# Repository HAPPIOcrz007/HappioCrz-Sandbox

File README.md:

# HappioCrz-Sandbox
a holderfor trials and learning zone for Happio-Projects and Happio-Wiki

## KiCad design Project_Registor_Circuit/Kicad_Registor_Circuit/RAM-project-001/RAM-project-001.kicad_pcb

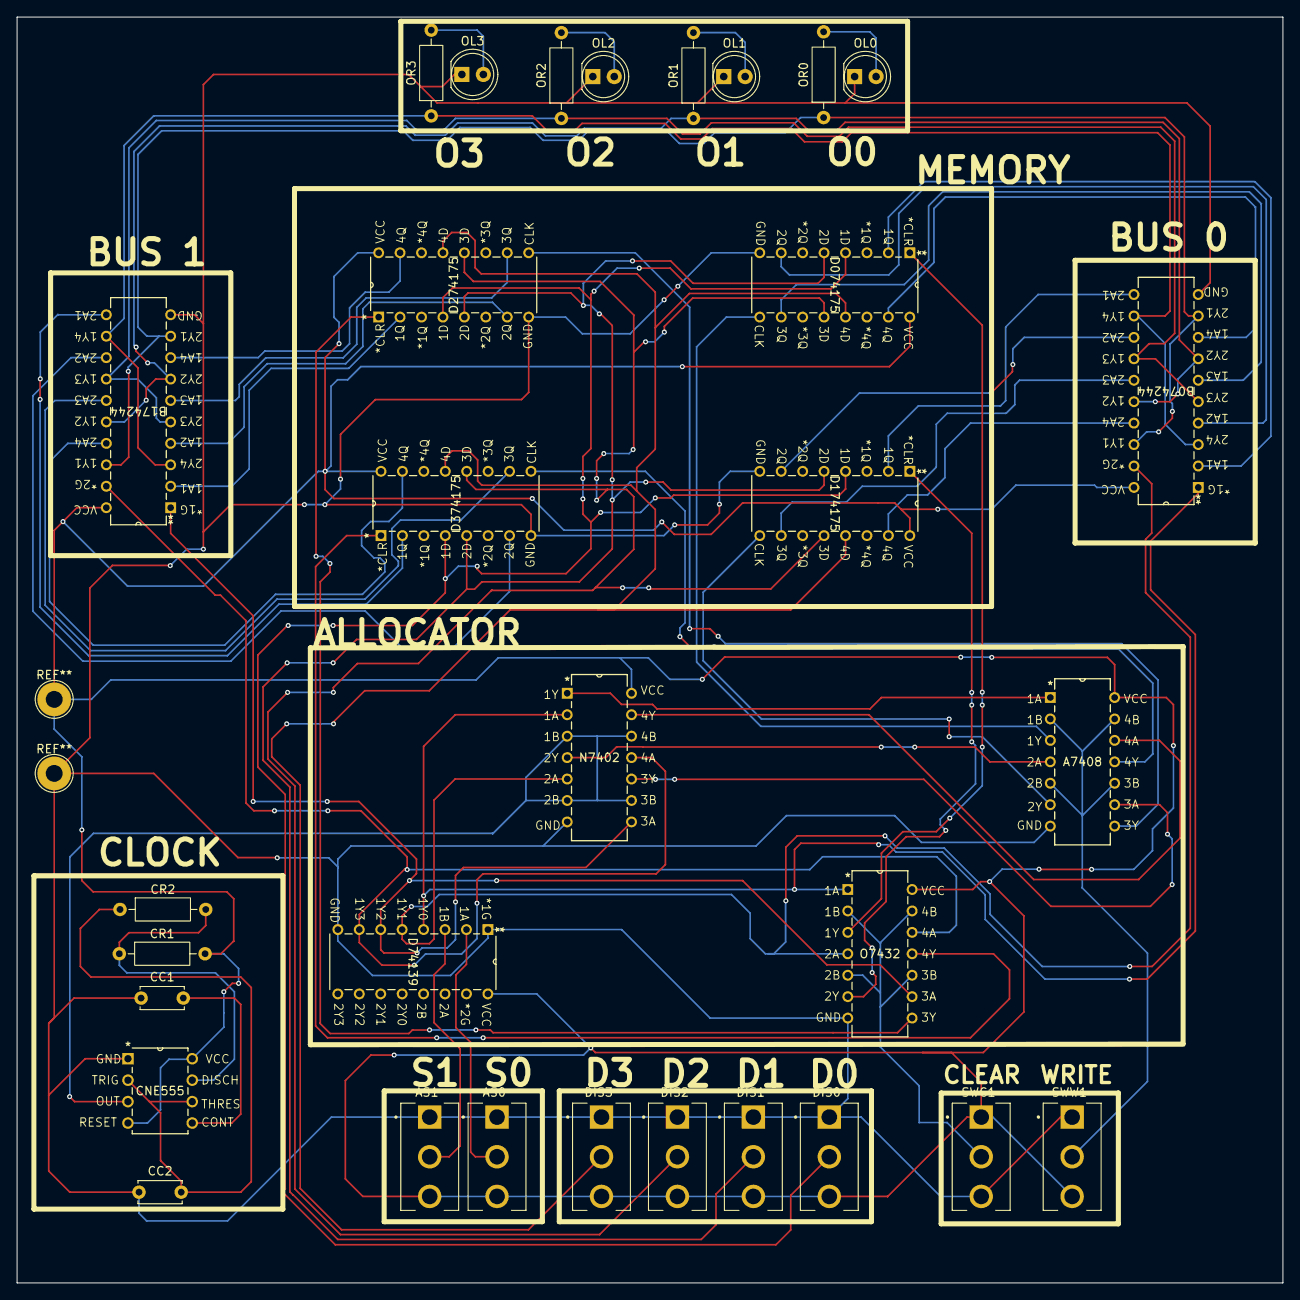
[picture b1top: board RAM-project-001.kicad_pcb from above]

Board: 2 copper layers, 150.0 x 150.0 mm, 31 parts (0 on the bottom side), 54 nets.

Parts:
A7408: A7408; SN74LS08N
AS0: AS0; SW_100SP1T1B4M2QE
AS1: AS1; SW_100SP1T1B4M2QE
B074244: B074244; SN74LS244N
B174244: B174244; SN74LS244N
CC1: CC1; C_Disc_D5.0mm_W2.5mm_P5.00mm
CC2: CC2; C_Disc_D5.0mm_W2.5mm_P5.00mm
CNE555: CNE555; NE555P
CR1: CR1; R_Axial_DIN0207_L6.3mm_D2.5mm_P10.16mm_Horizontal
CR2: CR2; R_Axial_DIN0207_L6.3mm_D2.5mm_P10.16mm_Horizontal
D74139: D74139; SN74LS139AN
D074175: D074175; SN74LS175N
D174175: D174175; SN74LS175N
D274175: D274175; SN74LS175N
D374175: D374175; SN74LS175N
DIS0: DIS0; SW_100SP1T1B4M2QE
DIS1: DIS1; SW_100SP1T1B4M2QE
DIS2: DIS2; SW_100SP1T1B4M2QE
DIS3: DIS3; SW_100SP1T1B4M2QE
N7402: N7402; SN7402N
O7432: O7432; SN7432N
OL0, OL1, OL2, OL3: CQY99; LED_D5.0mm
OR0, OR1, OR2, OR3: R; R_Axial_DIN0207_L6.3mm_D2.5mm_P10.16mm_Horizontal
SWC1: SWC; SW_100SP1T1B4M2QE
SWW1: SWW; SW_100SP1T1B4M2QE

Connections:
+5V: A7408.14 (VCC), AS0.3, AS1.3, B074244.20 (VCC), B174244.20 (VCC), CNE555.4 (RESET), CNE555.8 (VCC), CR1.2, D74139.16 (VCC), D074175.16 (VCC), D174175.16 (VCC), D274175.16 (VCC), D374175.16 (VCC), DIS0.3, DIS1.3, DIS2.3, DIS3.3, N7402.14 (VCC), O7432.14 (VCC), SWC1.1, SWW1.3
/C0: D074175.1 (*CLR), O7432.3 (1Y)
/C1: D174175.1 (*CLR), O7432.6 (2Y)
/C2: D274175.1 (*CLR), O7432.8 (3Y)
/C3: D374175.1 (*CLR), O7432.11 (4Y)
/D0: D074175.4 (1D), D174175.4 (1D), D274175.4 (1D), D374175.4 (1D), DIS0.2
/D1: D074175.5 (2D), D174175.5 (2D), D274175.5 (2D), D374175.5 (2D), DIS1.2
/D2: D074175.12 (3D), D174175.12 (3D), D274175.12 (3D), D374175.12 (3D), DIS2.2
/D3: D074175.13 (4D), D174175.13 (4D), D274175.13 (4D), D374175.13 (4D), DIS3.2
/S0: B074244.1 (*1G), D74139.4 (1Y0), N7402.2 (1A), O7432.1 (1A)
/S1: B074244.19 (*G/2G), D74139.5 (1Y1), N7402.5 (2A), O7432.4 (2A)
/S2: B174244.1 (*1G), D74139.6 (1Y2), N7402.8 (3A), O7432.9 (3A)
/S3: B174244.19 (*G/2G), D74139.7 (1Y3), N7402.11 (4A), O7432.12 (4A)
/W0: A7408.3 (1Y), D074175.9 (CLK)
/W1: A7408.6 (2Y), D174175.9 (CLK)
/W2: A7408.8 (3Y), D274175.9 (CLK)
/W3: A7408.11 (4Y), D374175.9 (CLK)
GND: A7408.7 (GND), AS0.1, AS1.1, B074244.10 (GND), B174244.10 (GND), CC1.1, CC2.1, CNE555.1 (GND), D74139.1 (1C), D74139.8 (GND), D074175.8 (GND), D174175.8 (GND), D274175.8 (GND), D374175.8 (GND), DIS0.1, DIS1.1, DIS2.1, DIS3.1, N7402.7 (GND), O7432.7 (GND), OL0.1 (K), OL1.1 (K), OL2.1 (K), OL3.1 (K), SWC1.3, SWW1.1
unnamed: A7408.1 (1A), N7402.1 (1Y)
unnamed: A7408.2 (1B), A7408.5 (2B), A7408.10 (3B), A7408.13 (4B), SWW1.2
unnamed: A7408.4 (2A), N7402.4 (2Y)
unnamed: A7408.9 (3A), N7402.10 (3Y)
unnamed: A7408.12 (4A), N7402.13 (4Y)
unnamed: B074244.2 (1A1), D074175.2 (1Q)
unnamed: B074244.4 (1A2), D074175.7 (2Q)
unnamed: B074244.6 (1A3), D074175.10 (3Q)
unnamed: B074244.8 (1A4), D074175.15 (4Q)
unnamed: B074244.9 (2Y1), B074244.18 (1Y1), B174244.9 (2Y1), B174244.18 (1Y1), OR0.1
unnamed: B074244.7 (2Y2), B074244.16 (1Y2), B174244.7 (2Y2), B174244.16 (1Y2), OR1.1
unnamed: B074244.5 (2Y3), B074244.14 (1Y3), B174244.5 (2Y3), B174244.14 (1Y3), OR2.1
unnamed: B074244.3 (2Y4), B074244.12 (1Y4), B174244.3 (2Y4), B174244.12 (1Y4), OR3.1
unnamed: B074244.11 (2A1), D174175.2 (1Q)
unnamed: B074244.13 (2A2), D174175.7 (2Q)
unnamed: B074244.15 (2A3), D174175.10 (3Q)
unnamed: B074244.17 (2A4), D174175.15 (4Q)
unnamed: B174244.2 (1A1), D274175.2 (1Q)
unnamed: B174244.4 (1A2), D274175.7 (2Q)
unnamed: B174244.6 (1A3), D274175.10 (3Q)
unnamed: B174244.8 (1A4), D274175.15 (4Q)
unnamed: B174244.11 (2A1), D374175.2 (1Q)
unnamed: B174244.13 (2A2), D374175.7 (2Q)
unnamed: B174244.15 (2A3), D374175.10 (3Q)
unnamed: B174244.17 (2A4), D374175.15 (4Q)
unnamed: CC1.2, CNE555.5 (CONT)
unnamed: CNE555.7 (DISCH), CR1.1, CR2.2
unnamed: CNE555.3 (OUT), N7402.3 (1B), N7402.6 (2B), N7402.9 (3B), N7402.12 (4B)
unnamed: CC2.2, CNE555.2 (TRIG), CNE555.6 (THRES), CR2.1
unnamed: AS0.2, D74139.2 (1A)
unnamed: AS1.2, D74139.3 (1B)
unnamed: O7432.2 (1B), O7432.5 (2B), O7432.10 (3B), O7432.13 (4B), SWC1.2
unnamed: OL0.2 (A), OR0.2
unnamed: OL1.2 (A), OR1.2
unnamed: OL2.2 (A), OR2.2
unnamed: OL3.2 (A), OR3.2

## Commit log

2025-06-29 added node template
2025-07-01 updated vs code python settings
2025-07-07 added a bash script to make copy of project in a zip file so thaat a complete copy can be stored and be reverted to back
2025-10-03 GitButler Workspace Commit
    This is a merge commit the virtual branches in your workspace.
    Due to GitButler managing multiple virtual branches, you cannot switch back and
    forth between git branches and virtual branches easily.
    If you switch to another branch, GitButler will need to be reinitialized.
    If you commit on this branch, GitButler will throw it away.
    Here are the branches that are currently applied:
2025-10-12 comitting
2025-10-17 completed getting orders completed completing affirmative orders
2025-10-19 Added superior copy moco.py
2026-01-14 New collaboration
2026-01-14 Add Project_ashai files
2026-01-15 Add Project_ashai files by HMR
2026-01-16 Refactor main.py for improved file processing
    Refactor main.py to enhance functionality and improve file handling.
2026-01-16 Restructured Project_ashai
2026-01-16 Save local changes before merge
2026-01-19 updating files for html steructure
2026-01-19 updated files 16:30 19/01/2026
2026-01-22 redesigned and finalised the files of Project-Ashai
2026-01-22 updated problem sheet, removed all tle problems - 800 [ all ] - 900 [ 1,2,3,4,6,7,8,9,10,11 ]
2026-01-22 moved Projec-Ashai to Projects started new project - RAM - Stock simulator
2026-01-23 updated files
2026-02-18 listed all parts ffor ram project with datasheets
2026-02-20 a next stage of ram project done
2026-02-21 done base design of Ram Project
2026-03-03 made base structure for stock simulation project
2026-03-03 changes to .gitignore
2026-03-04 made base structure for stock market sim made structural and dir changes to ram project
2026-03-19 amazing updates to both ram and stock market project - ram design and components done - stock market - build base .h file and tried some rusting
2026-03-20 update to Project Ram
2026-03-26 completed pcb design of the Registor Project
2026-03-26 Remove unused Project_Ram_Circuit files
